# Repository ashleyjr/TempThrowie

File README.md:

# TempThrowie: Install

## MCUs

   - SDCC : mcs51/z80/z180/r2k/r3ka/gbz80/tlcs90/ds390/TININative/ds400/hc08/s08/stm8 3.5.0
   - SimplicityStudio_v5 flash8051

      - Download from Silicon Labs website
      - Requires 8-bit additonal tools which can be downloaded inside the studio 

   - Silicon Labs 8-Bit USB Debug Adapter

## Basestation (Raspberry Pi)

   - Basestation is a Raspberry Pi Model B Plus Rev 1.2
   - Fresh install of Raspbian GNU/Linux 11 (bullseye)
   - pip install matplotlib
   - sudo apt-get install libatlas-base-dev
   - pip install numpy --upgrade
   - sudo apt install apache2 -y
   - sudo apt-get install php libapache2-mod-php 
   - Config:

```
(21:10 pi@raspberrypi ~) > crontab -l | tail -n 1
*/20 * * * * cd /home/pi/TempThrowie/receiver/software/base/; python throwieAnalysis.py --stats --log stats.log; python throwieAnalysis.py --plotbatttoday --out ../webpage/batttoday.png --log batttoday.log; python throwieAnalysis.py --plottemptoday --out ../webpage/temptoday.png --log temptoday.log; python throwieAnalysis.py --plotbattweek --out ../webpage/battweek.png --log battweek.log; python throwieAnalysis.py --plottempweek --out ../webpage/tempweek.png --log tempweek.log
(21:10 pi@raspberrypi ~) > tail -n 5 /etc/rc.local 
# Run TempThrowie UART monitor
rm /home/pi/TempThrowie/receiver/software/base/throwie.db
cd /home/pi/TempThrowie/receiver/software/base; python throwieLogging.py &

exit 0
(21:10 pi@raspberrypi ~) > cat /etc/apache2/sites-available/000-default.conf | grep DocumentRoot
	DocumentRoot /home/pi/TempThrowie/receiver/software/webpage/
(21:10 pi@raspberrypi ~) > cat /etc/apache2/apache2.conf | grep TempThrowie -A4
<Directory /home/pi/TempThrowie/receiver/software/webpage/>
	Options Indexes FollowSymLinks
	AllowOverride None
	Require all granted
</Directory>
(21:10 pi@raspberrypi ~) > 
```

## Basestation (Laptop)

   - MacBook Pro 2019
   - Virtual Box Virtual Machine
   - Ubuntu 20.04.4 LTS
   - sudo update-alternatives --install /usr/bin/python python /usr/bin/python3 10
   - sudo apt-get install python3-pip
   - python -m pip install pyserial 
   - python -m pip install matplotlib
   - sudo apt install imagemagick-6.q16

# TempThrowie: Spec

## Throwie

### Transmitter

#### Physical

   - Amplitude Modulated (AM) 
   - On Off Keying (OOK) 
   - 433MHz carrier
   - Asynchronous 1K bits per second (pbs) bit stream 

#### Packet

   - A packet is formed of 64 bytes
   - Each byte is sent least signifiant bit first in the following order
     with no spaces

      - Byte0:  The preamble code 0xAA/0x10101010
         ...
      - Byte58: The preamble code 0xAA/0x10101010
      - Byte59: The start code 0x6A/0b01101010
      - Byte60: The throwie identity (ID)
      - Byte61: The temperature reading
      - Byte62: The battery reading
      - Byte63: XOR (Byte3 ^ (Byte2 ^ Byte1))  

#### Collisions

   - Within a collection of throwies the transmit intervals are asynchronous
   
   - A packet is transmitted every 10 minutes
   
   - The 40 bits in each packet takes 40ms to transmit

   - Probability of a collision

      - x = ((n-1) * d) / t

      - n = Number of thowies in collection

      - d = Duration of tranmissions (seconds) = 0.04

      - t = Transmit interval (seconds) = 600

   - Probability of failure when n is

      - 2:     x = 0,04 / 600          = 6.6 * 10^-5
      - 10:    x = (9 * 0,04) / 600    = 6   * 10^-4
      - 256:   x = (255 * 0,04) / 600  = 1.7 * 10^-2
   
   - Mean time between failure at 144 transmissions a day when n is
      
      - 2:     105 days 
      - 10:    12 days    
      - 256:   0.41 days

   - **This does not include failures caused by interference from other devices**

### Measurements

#### Temperature

   - Range between -10C and 50C
   - In the transmitted byte encoding each increment is worth 0.234C ((50 - (-10))/256) 
   - The offset is not calibrated

#### Battery

   - Range between 3.3V and 7V
   - In the transmitted byte encoding each increment is worth 0.014V ((7 - 3.3)/256) 
   - The offset is calibrated and 0 represent the lower voltage

## Receiver

### The serial port 
   
   - Has a baud rate of 115200
   - Transmits 1 start bit 
   - Transmits 8 bit data frame most significant bit first 
   
### Hardware

   - TODO: Spec RF receiver

   - The microcontroller is continually monitoring the output of the receiver 
   - The sample rate is 2KHz 
   - There is a pattern detector searching for the following 8 bytes

      - Byte0: 0b?1?0?1?0
         ...
      - Bytes6: 0b?1?0?1?0
      - Bytes7: 0b?0?1?1?0

   - When the code is detected the next 8 bytes are placed in to a buffer
     and immediately transmitted over the serial port
   - When the last byte is transmitted the microcontroller goes back to 
     pattern detection

### Computer

   - The receiver hardware is connected to a host computer using a serial port   
   - There are two scripts running on the computer

      - The *Logging Script* is continuously running and writing data 
      - The *Analysis Script* may be envoked at anytime and reads the data
       
#### Logging Script

   - The script is called *throwieLogging.py*
   - The serial port is continuously monitored 
   
      - When a frame is received a timeout window opens 
      - The window closes when no frame is recieved for 2 seconds
      - While the window is open all frames received are placed in to a buffer
      - The depth of the buffer is 500 Bytes

         - As the sample rate of the microcontroller is 2KHz it is impossible to 
           overflow this buffer

   - When the timeout window closes 
      
      - A string is created by draining the buffer
      - Each byte is converted to a two character hexadecimal string   
      - More bytes are added to the right hand side of the string 
      - When the buffer is fully drained the left hand side contains the first byte
        recieved and right hand side contained the last byte recieved

   - The string is written to a log file

      - The file is called **throwie_YYYYMMDD_HHSS.log**

         - Y = Year
         - M = Month
         - D = Day
         - H = Hour (24h)
         - M = Minute

      - The file is located in the same directory as the script  

#### Analysis Script

   - The script is called *throwieAnalysis.py*
   - The setup phase

      - Will open every log file in chronological order
      - Create a list of transmissions containing 

         - The date
         - The time
         - The 

      - If the log file contains 8 bytes of data it will analyse

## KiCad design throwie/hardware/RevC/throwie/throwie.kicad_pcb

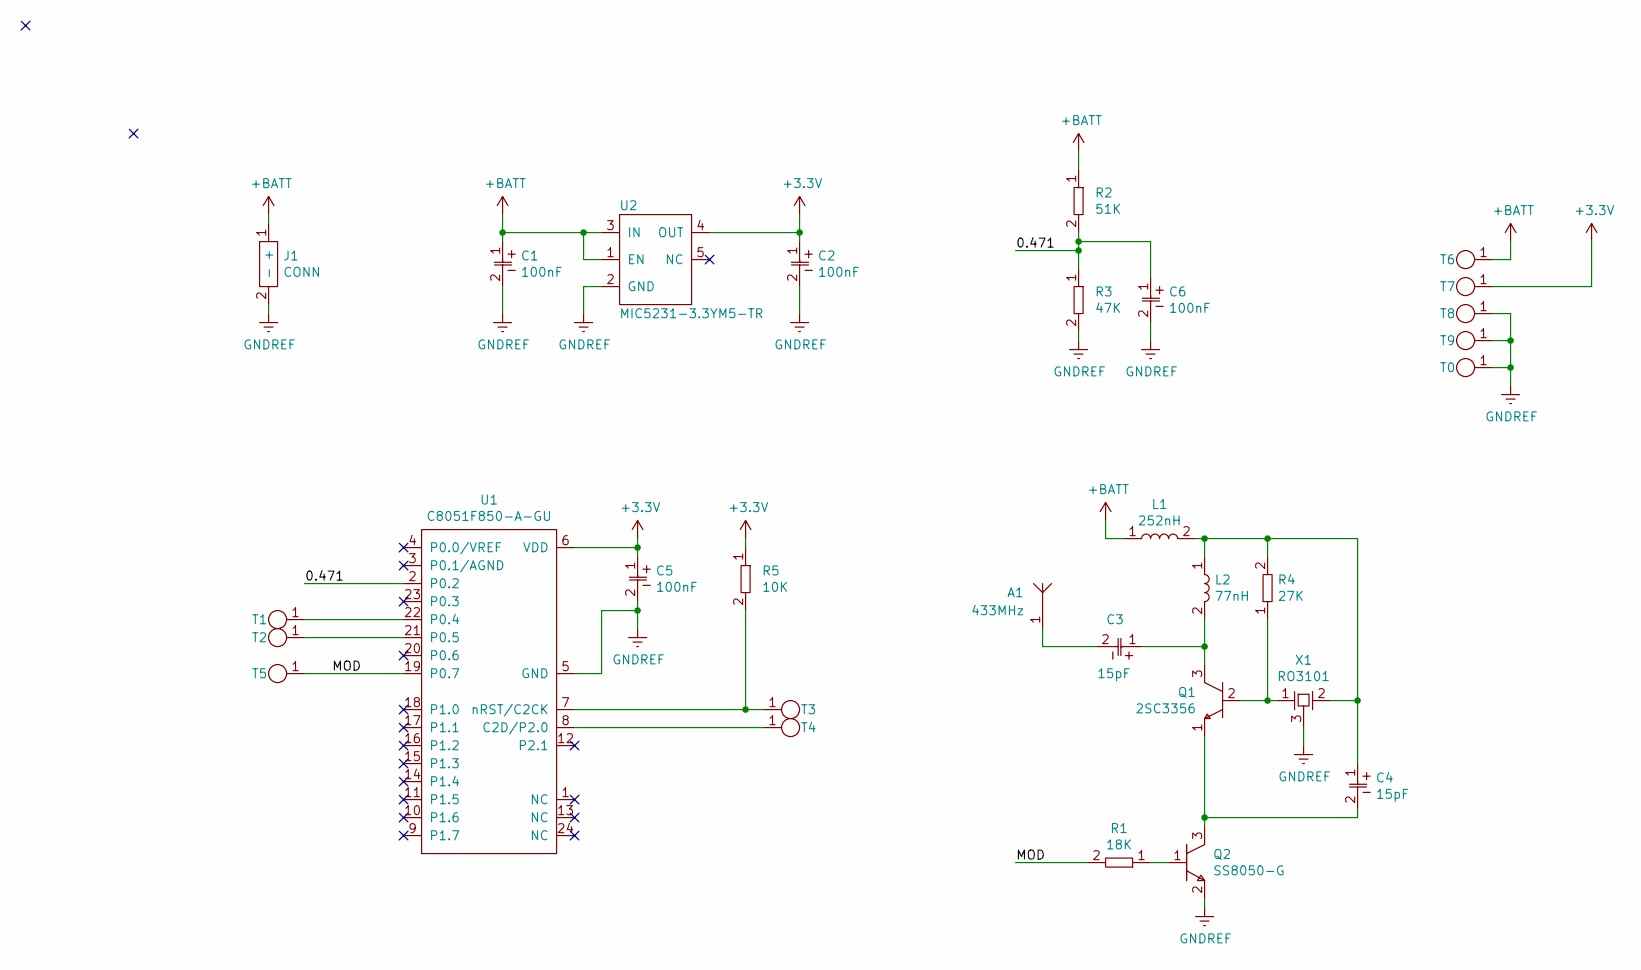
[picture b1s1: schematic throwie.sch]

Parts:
A1: 433MHz
C1, C2, C3, C4, C5, C6: CAP_0603; 0603
J1: CONN
L1: 252nH
L2: 77nH
Q1: 2SC3356
Q2: SS8050-G
R1, R2, R3, R4, R5: RES_0603; 0603
T0, T1, T2, T3, T4, T5, T6, T7, T8, T9: TestPoints; TestPoint
U1: C8051F850-A-GU
U2: MIC5231-3.3YM5-TR; MIC5231
X1: RO3101; R03101

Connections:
+3V3: C2.1, C5.1, R5.1, T7.1, U1.6 (VDD), U2.4 (OUT)
+BATT: C1.1, J1.1 (+), L1.1, R2.1, T6.1, U2.1 (EN), U2.3 (IN)
/0.471: C6.1, R2.2, R3.1, U1.2 (P0.2)
/MOD: R1.2, T5.1, U1.19 (P0.7)
GNDREF: C1.2, C2.2, C5.2, C6.2, J1.2 (-), Q2.2, R3.2, T0.1, T8.1, T9.1, U1.5 (GND), U2.2 (GND), X1.3
unnamed: A1.1, C3.2
unnamed: C3.1, L2.2, Q1.3
unnamed: C4.1, L1.2, L2.1, R4.2, X1.2
unnamed: C4.2, Q1.1, Q2.3
unnamed: Q1.2, R4.1, X1.1
unnamed: Q2.1, R1.1
unnamed: R5.2, T3.1, U1.7 (nRST/C2CK)
unnamed: T1.1, U1.22 (P0.4)
unnamed: T2.1, U1.21 (P0.5)
unnamed: T4.1, U1.8 (C2D/P2.0)

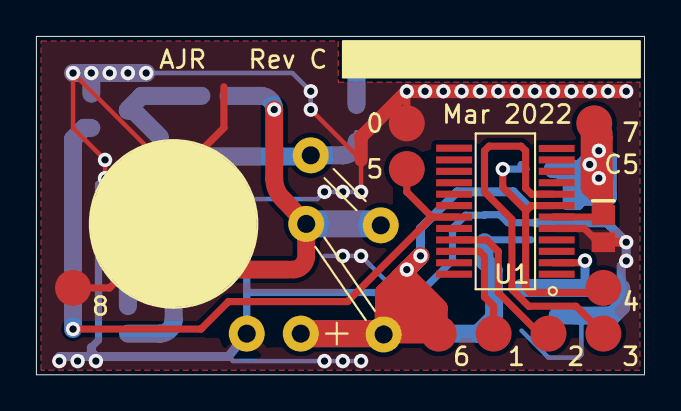
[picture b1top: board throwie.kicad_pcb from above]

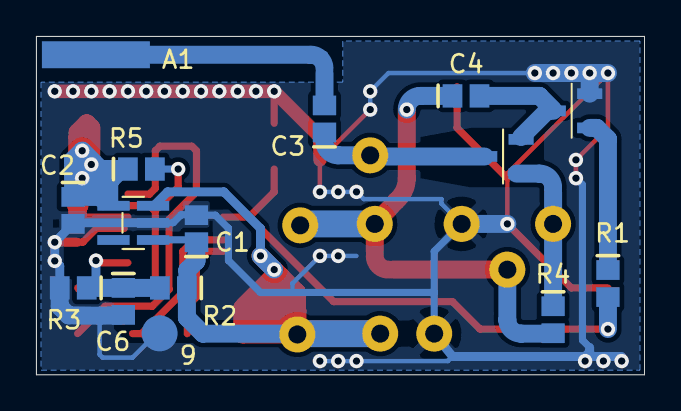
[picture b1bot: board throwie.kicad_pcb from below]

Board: 2 copper layers, 33.8 x 18.8 mm, 30 parts (15 on the bottom side), 15 nets.

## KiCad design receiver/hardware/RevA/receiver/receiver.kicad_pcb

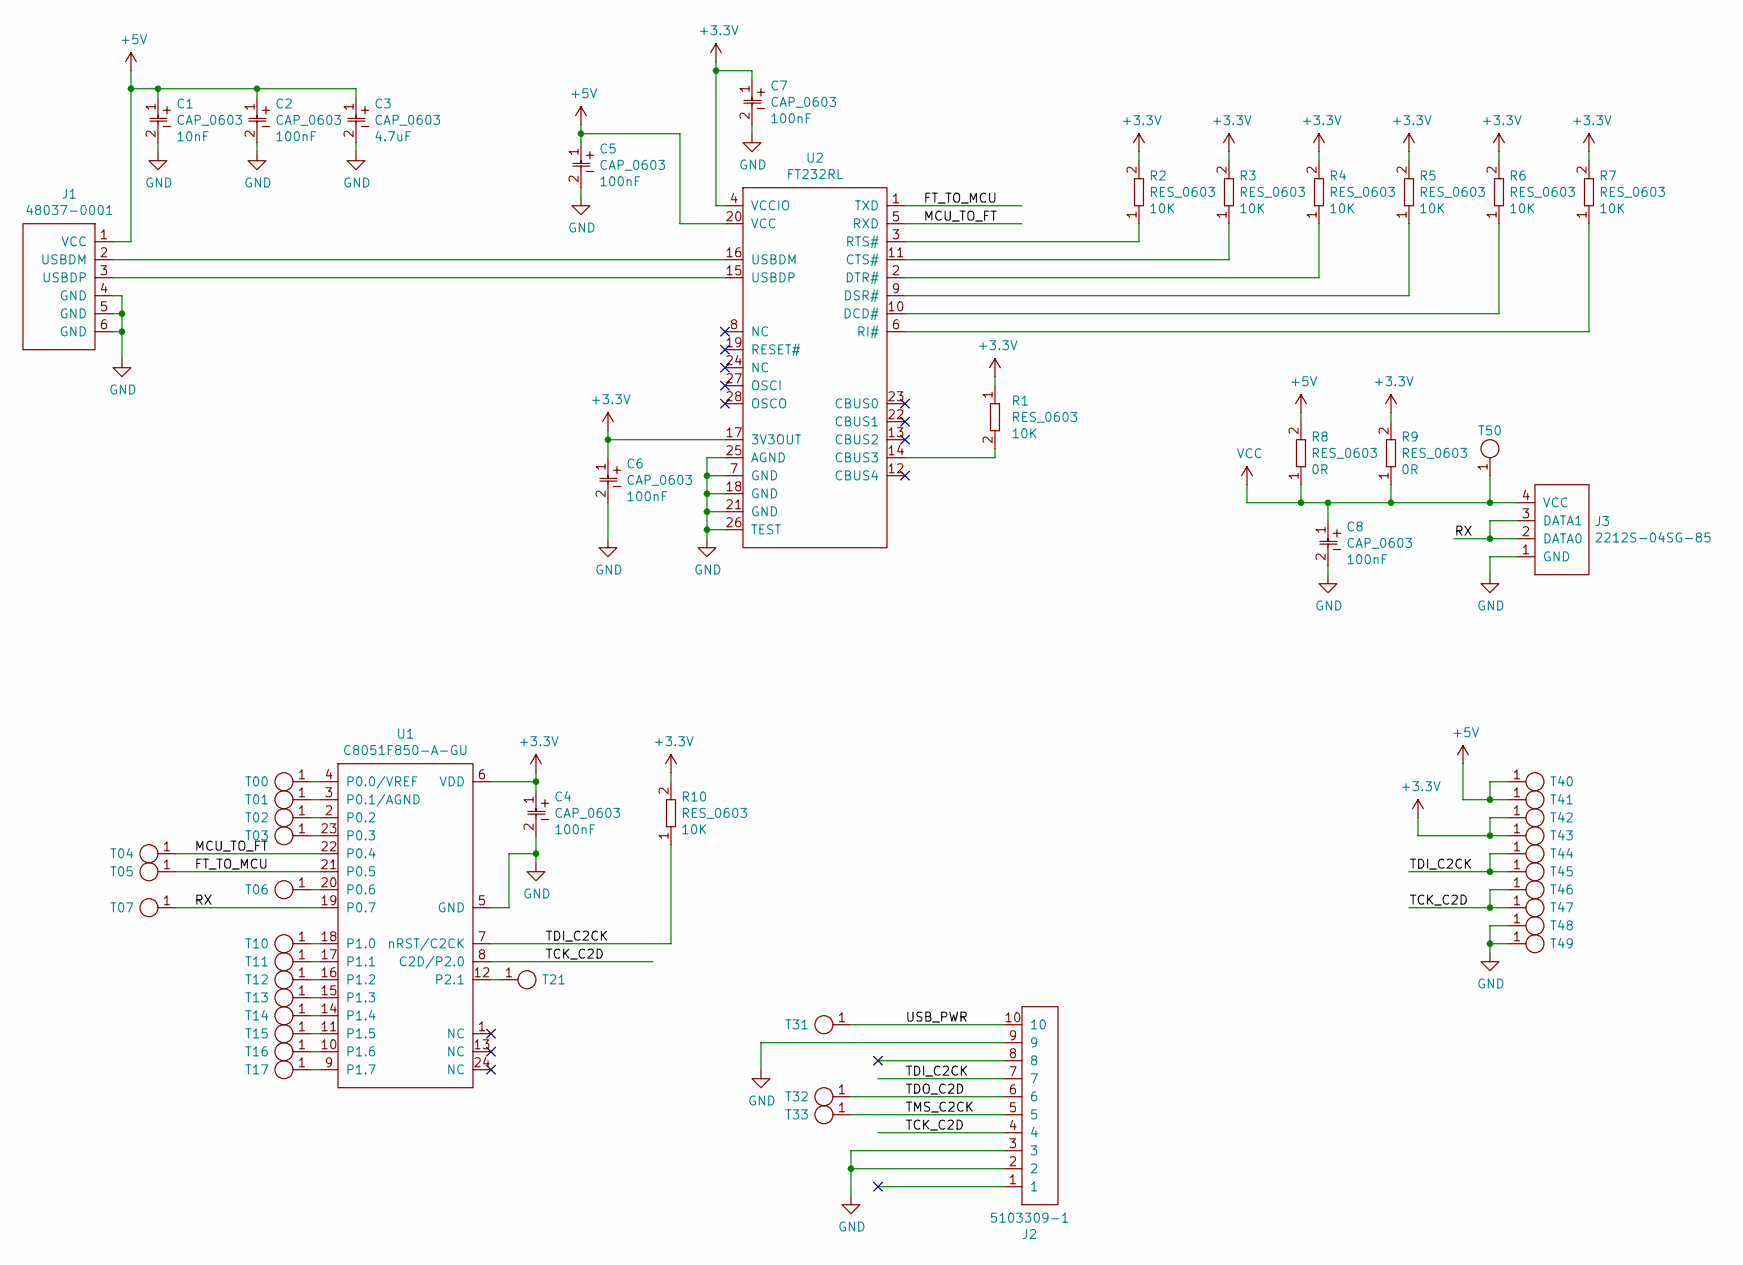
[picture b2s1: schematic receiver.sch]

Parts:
C1, C2, C3, C4, C5, C6, C7, C8: CAP_0603; 0603
J1: 48037-0001
J2: 5103309-1
J3: 2212S-04SG-85
R1, R2, R3, R4, R5, R6, R7, R8, R9, R10: RES_0603; 0603
T00, T01, T02, T03, T04, T05, T06, T07, T10, T11, T12, T13, T14, T15, T16, T17, T21, T31, T32, T33, T40, T41, T42, T43, T44, T45, T46, T47, T48, T49, T50: TestPoints; TestPoint
U1: C8051F850-A-GU
U2: FT232RL

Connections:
+3V3: C4.1, C6.1, C7.1, R1.1, R2.2, R3.2, R4.2, R5.2, R6.2, R7.2, R9.2, R10.2, T42.1, T43.1, U1.6 (VDD), U2.4 (VCCIO), U2.17 (3V3OUT)
+5V: C1.1, C2.1, C3.1, C5.1, J1.1 (VCC), R8.2, T40.1, T41.1, U2.20 (VCC)
/FT_TO_MCU: T05.1, U1.21 (P0.5), U2.1 (TXD)
/MCU_TO_FT: T04.1, U1.22 (P0.4), U2.5 (RXD)
/RX: J3.2 (DATA0), J3.3 (DATA1), T07.1, U1.19 (P0.7)
/TCK_C2D: J2.4, T46.1, T47.1, U1.8 (C2D/P2.0)
/TDI_C2CK: J2.7, R10.1, T44.1, T45.1, U1.7 (nRST/C2CK)
/TDO_C2D: J2.6, T32.1
/TMS_C2CK: J2.5, T33.1
/USB_PWR: J2.10, T31.1
GND: C1.2, C2.2, C3.2, C4.2, C5.2, C6.2, C7.2, C8.2, J1.4 (GND), J1.5 (GND), J1.6 (GND), J2.2, J2.3, J2.9, J3.1 (GND), T48.1, T49.1, U1.5 (GND), U2.7 (GND), U2.18 (GND), U2.21 (GND), U2.25 (AGND), U2.26 (TEST)
unnamed: J1.2 (USBDM), U2.16 (USBDM)
unnamed: J1.3 (USBDP), U2.15 (USBDP)
unnamed: R1.2, U2.14 (CBUS3)
unnamed: R2.1, U2.3 (RTS#)
unnamed: R3.1, U2.11 (CTS#)
unnamed: R4.1, U2.2 (DTR#)
unnamed: R5.1, U2.9 (DSR#)
unnamed: R6.1, U2.10 (DCD#)
unnamed: R7.1, U2.6 (RI#)
unnamed: T00.1, U1.4 (P0.0/VREF)
unnamed: T01.1, U1.3 (P0.1/AGND)
unnamed: T02.1, U1.2 (P0.2)
unnamed: T03.1, U1.23 (P0.3)
unnamed: T06.1, U1.20 (P0.6)
unnamed: T10.1, U1.18 (P1.0)
unnamed: T11.1, U1.17 (P1.1)
unnamed: T12.1, U1.16 (P1.2)
unnamed: T13.1, U1.15 (P1.3)
unnamed: T14.1, U1.14 (P1.4)
unnamed: T15.1, U1.11 (P1.5)
unnamed: T16.1, U1.10 (P1.6)
unnamed: T17.1, U1.9 (P1.7)
unnamed: T21.1, U1.12 (P2.1)
VCC: C8.1, J3.4 (VCC), R8.1, R9.1, T50.1

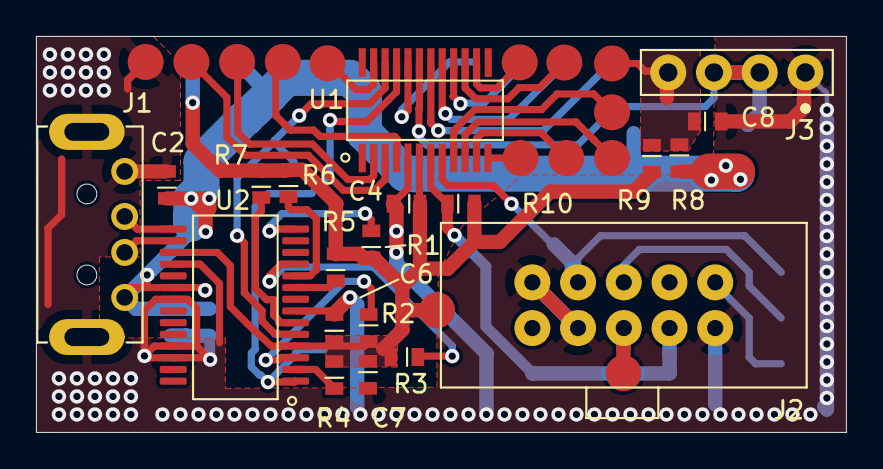
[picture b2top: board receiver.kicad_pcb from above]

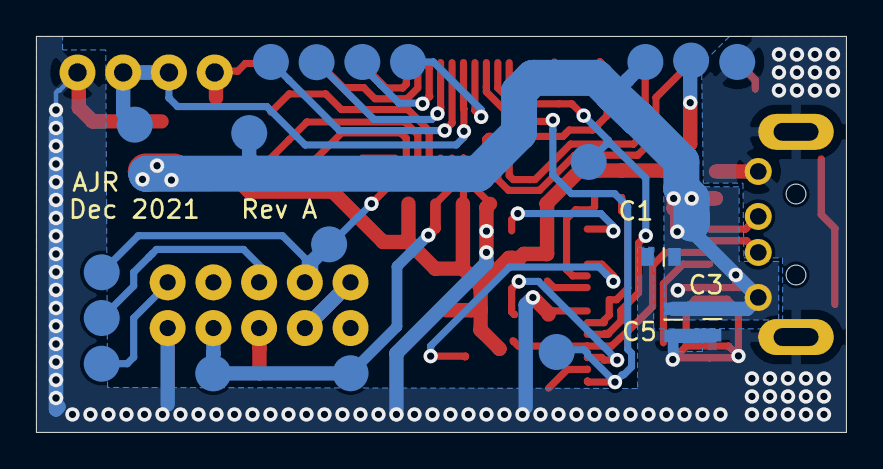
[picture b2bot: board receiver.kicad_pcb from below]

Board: 2 copper layers, 45.0 x 22.0 mm, 54 parts (20 on the bottom side), 35 nets.

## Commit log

2017-03-24 Back end graph for temp throwie
2017-03-25 pChart class
2017-03-25 submission of url for testing
2017-03-25 adjust for more vals
2021-09-27 remove
2021-10-06 fab output
2021-10-07 empty c
2021-10-07 sleep
2021-10-07 start caseworks
2021-10-11 uart working
2021-10-11 started frame build
2021-10-12 update bit stream
2021-10-12 readme
2021-10-12 more details
2021-10-20 debug tidy
2021-10-21 data
2021-11-10 fix adc
2021-11-18 todos
2021-11-18 start RevB pcb
2021-11-18 update libs
2021-11-22 schematic notes
2021-11-23 more layout
2021-11-24 final layout
2021-11-24 more silk
2021-11-24 gen revB fab output
2021-11-24 drill file
2021-11-29 Started receiver
2021-11-29 start sqlite db
2021-11-30 updare spec
2021-12-02 more codes
2021-12-03 more spec
2021-12-04 update throwie mcu
2021-12-05 started sample
2021-12-05 the buffer working
2021-12-06 clear buffer
2021-12-10 pll model
2021-12-10 vco model
2021-12-13 locking
2021-12-13 tidy
2021-12-14 start receiver pcb
2021-12-16 Added FT232RL
2021-12-17 ftdi and usb
2021-12-20 add connector
2021-12-21 connectors
2021-12-24 edge cuts
2021-12-27 finish layout
2021-12-27 updated with fab output
2021-12-28 test
2021-12-28 set throwie data rate to 1KHz
2021-12-28 add model to C receiver build
2021-12-28 import C
2021-12-28 c in model
2021-12-29 LPF optimise
2021-12-29 scaled lpf
2021-12-29 timestep
2021-12-29 reduce to 5KHz
2022-01-04 PLL not running fast enough, change phase shift
2022-01-04 constants
2022-01-04 phase lock
2022-01-06 mcu locking
2022-01-15 todo
2022-01-16 nice lock
2022-01-16 pushing over UART
2022-01-16 c tody
2022-01-16 Added logging script
2022-01-17 graphs
2022-01-19 find functions
2022-01-23 always have sample pin
2022-01-25 add git ignore
2022-01-25 log file search
2022-01-25 add histogram
2022-01-29 change to manchester encoding
2022-01-29 new demod scheme
2022-02-01 filter lof
2022-02-01 analysis
2022-02-01 state machine
2022-02-02 more analysis
2022-02-04 decode
2022-02-05 decoder working
2022-02-08 uart hex
2022-02-08 start code
2022-02-12 fix nibble order
2022-02-12 fix batt adc
2022-02-15 ADCs working
2022-02-15 rx hex
2022-02-16 update the pickle script
2022-02-19 logging
2022-02-19 add bash script
2022-02-19 add args
2022-02-19 run on startup
2022-02-21 store datetime
2022-02-21 fix imports
2022-02-21 plotitng
2022-02-22 more graph features
2022-02-22 added intervas
2022-02-22 rm old files
2022-02-28 move to sqlite
2022-03-02 started prog jig
2022-03-08 add cuts for jig base
2022-03-08 start top part of jig
2022-03-08 jig cuts
2022-03-10 RevB jig base
2022-03-10 laptop help
2022-03-11 Another jog base
2022-03-11 started webpage
2022-03-11 numpy upgrade
2022-03-11 display graph
2022-03-15 output in to webpage
2022-03-18 logging updates
2022-03-18 another jog
2022-03-19 caseworks
2022-03-19 Another base spin
2022-03-20 rm on startup
2022-03-20 added a stats logs
2022-03-20 24h long graph
2022-03-20 fix y axis invert
2022-03-22 fix str/float
2022-03-23 RevD
2022-03-23 RevE
2022-03-25 cork on wrong side
2022-03-27 add date to title
2022-03-27 added week plots
2022-03-27 add week plots
2022-03-30 started throwie RevC
2022-03-30 added more test points
2022-03-31 increase pads, update fab output
2022-03-31 increase pads
2022-03-31 adjust floods
2022-03-31 fix back silk
2022-05-08 holes in jig top for probes
2022-11-26 Rev G
2022-11-26 rev H
2022-11-26 REV I
2022-11-27 RevJ
2022-11-27 rev k
2022-11-28 rev L
2022-11-30 silicon labs update
2022-12-10 rev f case
2022-12-18 RevG
